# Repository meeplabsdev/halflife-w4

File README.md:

# Music Player
|||
|---|---|

This is a embedded music player, which is designed to be on a desk and display the current track + lyrics over spotify or bluetooth (or others platforms).

# What it is
This project was created for week 4 of [halflife](https://halflife.hackclub.com/)! I designed the schematic and PCB using [KiCad](https://www.kicad.org/), as a hat for the [Orange Pi Zero 3](http://www.orangepi.org/orangepiwiki/index.php/Orange_Pi_Zero_3), which runs embedded linux so I was able to write the firmware in a form much closer to a traditional desktop application (and it can even be tested off the device with the gpio changes printed to the terminal). Originally, I was planning to incorporate the display driver onto the PCB, but I ended up just using a driver board from adafruit since it worked out to be cheaper.

# Hardware
Schematic:

PCB:

|||
|---|---|

# Software
[`firmware/`](firmware/) contains a rust project which can control the board (using wiringpi to set gpio states) and a GUI for the screen. Currently, it is just demo firmware to show how the device could be controlled but when I build this, I could update the firmware to something more useful.

# Case
I also designed a case for this to hold the screen at a reasonable angle, and to keep the boards in the back neat. (red is the screen)

|||
|---|---|

# Cost
This is a rough outline of the cost, see [`BOM.csv`](bom.csv) for more details.

| Part | Cost |
| --- | --- |
| [Screen](https://www.aliexpress.com/i/32772985029.html) | $16.92 |
| [Controller board](https://www.aliexpress.com/i/1005007586011837.html) | $33.00 |
| [Screen controller](https://thepihut.com/products/adafruit-tfp401-hdmi-dvi-decoder-to-40-pin-ttl-breakout-with-touch) | $38.38 |
| [HDMI adapter](https://www.aliexpress.com/item/1005006253497000.html) | $3.19 |
| [Power adapter](https://www.aliexpress.com/item/1005012406854301.html) | $4.05 |
| **Total + Shipping** | **$99.74** |

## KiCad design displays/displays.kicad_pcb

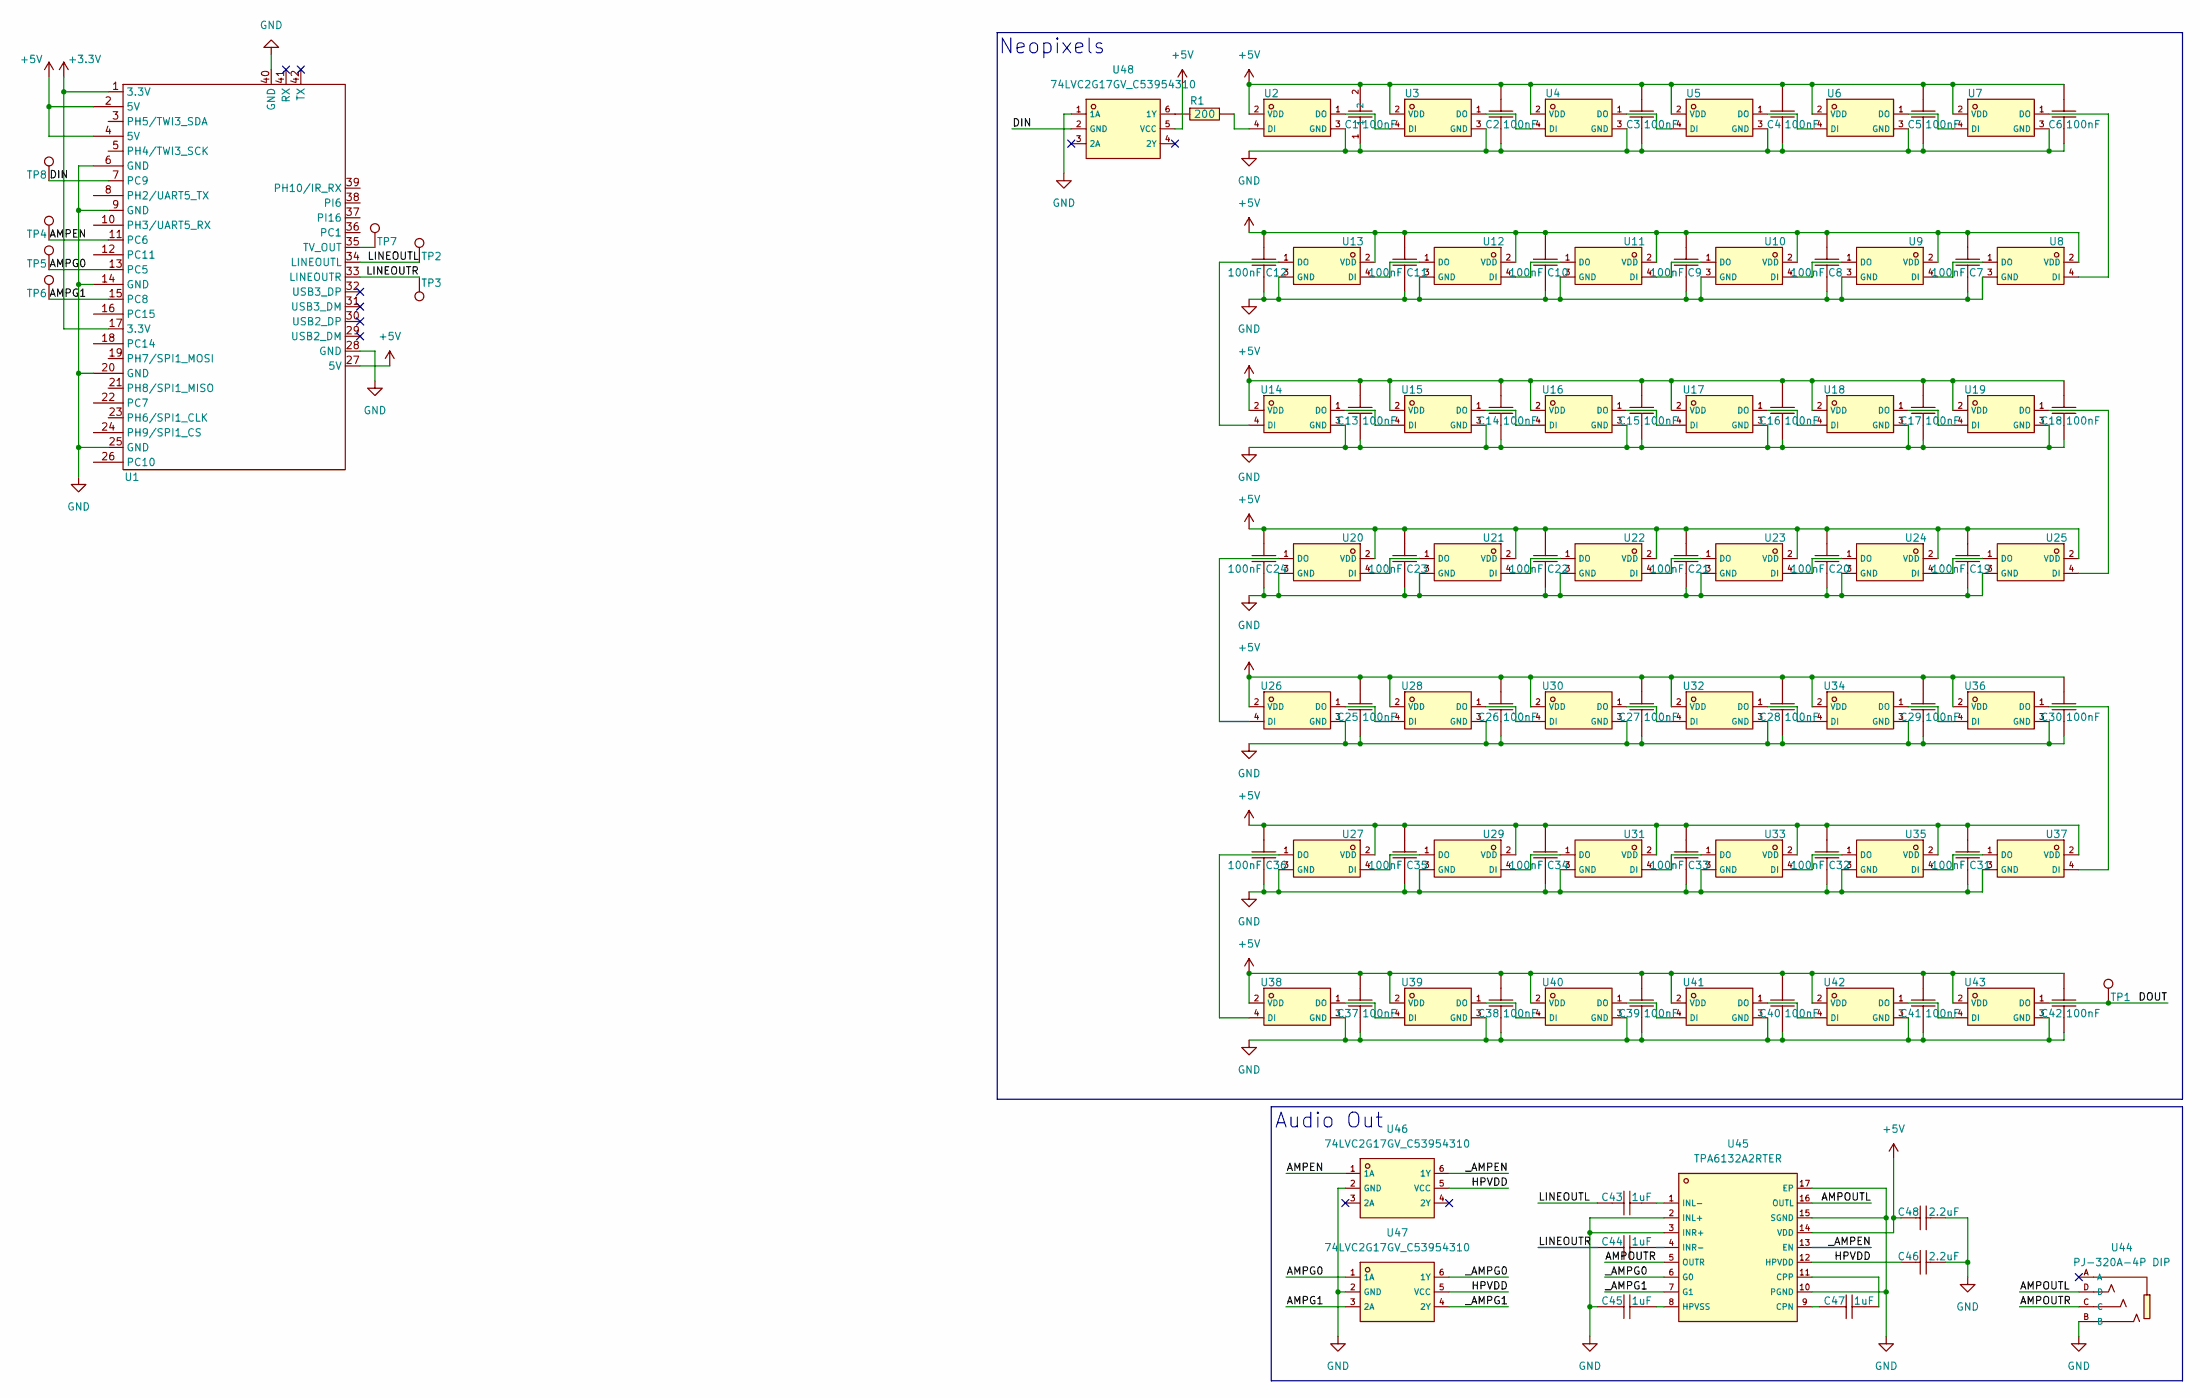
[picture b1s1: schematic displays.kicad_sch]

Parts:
C1, C2, C3, C4, C5, C6, C7, C8, C9, C10, C11, C12, C13, C14, C15, C16, C17, C18, C19, C20, C21, C22, C23, C24, C25, C26, C27, C28, C29, C30, C31, C32, C33, C34, C35, C36, C37, C38, C39, C40, C41, C42: 100nF; C1525_C0402; LCSC C1525
C43, C44, C45, C47: 1uF; C52923_C0402; LCSC C52923
C46, C48: 2.2uF; C23630_C0603; LCSC C23630
R1: 200; C25087_R0402; LCSC C25087
TP1, TP2, TP3, TP4, TP5, TP6, TP7, TP8: TestPoint; SolderWirePad_1x01_SMD_1x2mm
U1: Orange_Pi_Zero_3
U2, U3, U4, U5, U6, U7, U8, U9, U10, U11, U12, U13, U14, U15, U16, U17, U18, U19, U20, U21, U22, U23, U24, U25, U26, U27, U28, U29, U30, U31, U32, U33, U34, U35, U36, U37, U38, U39, U40, U41, U42, U43: TZ-H1010-RGB/A-BU08UF-TA1305NA/W109; C41347988_LED-SMD_4P-L1_0-W1_0_TZ-H1010-RGB-A-BU08UF-TA1305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; LCSC C41347988
U44: PJ-320A-4P DIP; C18185602_AUDIO-TH_PJ-320A-4P-DIP; LCSC C18185602
U45: TPA6132A2RTER; C69901_WQFN-16_L3_0-W3_0-P0_50-TL-EP1_6; LCSC C69901
U46, U47, U48: 74LVC2G17GV_C53954310; C53954310_SOT-23-6_L2_9-W1_6-P0_95-LS2_8-BR-3; LCSC C53954310

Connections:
+3.3V: U1.1 (3.3V), U1.17 (3.3V)
+5V: C1.2, C2.2, C3.2, C4.2, C5.2, C6.2, C7.2, C8.2, C9.2, C10.2, C11.2, C12.2, C13.2, C14.2, C15.2, C16.2, C17.2, C18.2, C19.2, C20.2, C21.2, C22.2, C23.2, C24.2, C25.2, C26.2, C27.2, C28.2, C29.2, C30.2, C31.2, C32.2, C33.2, C34.2, C35.2, C36.2, C37.2, C38.2, C39.2, C40.2, C41.2, C42.2, C48.1, U1.2 (5V), U1.4 (5V), U1.27 (5V), U2.2 (VDD), U3.2 (VDD), U4.2 (VDD), U5.2 (VDD), U6.2 (VDD), U7.2 (VDD), U8.2 (VDD), U9.2 (VDD), U10.2 (VDD), U11.2 (VDD), U12.2 (VDD), U13.2 (VDD), U14.2 (VDD), U15.2 (VDD), U16.2 (VDD), U17.2 (VDD), U18.2 (VDD), U19.2 (VDD), U20.2 (VDD), U21.2 (VDD), U22.2 (VDD), U23.2 (VDD), U24.2 (VDD), U25.2 (VDD), U26.2 (VDD), U27.2 (VDD), U28.2 (VDD), U29.2 (VDD), U30.2 (VDD), U31.2 (VDD), U32.2 (VDD), U33.2 (VDD), U34.2 (VDD), U35.2 (VDD), U36.2 (VDD), U37.2 (VDD), U38.2 (VDD), U39.2 (VDD), U40.2 (VDD), U41.2 (VDD), U42.2 (VDD), U43.2 (VDD), U45.14 (VDD), U48.5 (VCC)
/AMPEN: TP4.1 (1_1), U1.11 (PC6), U46.1 (1A)
/AMPG0: TP5.1 (1_1), U1.13 (PC5), U47.1 (1A)
/AMPG1: TP6.1 (1_1), U1.15 (PC8), U47.3 (2A)
/AMPOUTL: U44.D, U45.16 (OUTL)
/AMPOUTR: U44.C, U45.5 (OUTR)
/DIN: TP8.1 (1_1), U1.7 (PC9), U48.2 (GND)
/DOUT: TP1.1 (1_1), U43.1 (DO)
/HPVDD: C46.1, U45.12 (HPVDD), U46.5 (VCC), U47.5 (VCC)
/LINEOUTL: C43.1, TP2.1 (1_1), U1.34 (LINEOUTL)
/LINEOUTR: C44.1, TP3.1 (1_1), U1.33 (LINEOUTR)
/_AMPEN: U45.13 (EN), U46.6 (1Y)
/_AMPG0: U45.6 (G0), U47.6 (1Y)
/_AMPG1: U45.7 (G1), U47.4 (2Y)
GND: C1.1, C2.1, C3.1, C4.1, C5.1, C6.1, C7.1, C8.1, C9.1, C10.1, C11.1, C12.1, C13.1, C14.1, C15.1, C16.1, C17.1, C18.1, C19.1, C20.1, C21.1, C22.1, C23.1, C24.1, C25.1, C26.1, C27.1, C28.1, C29.1, C30.1, C31.1, C32.1, C33.1, C34.1, C35.1, C36.1, C37.1, C38.1, C39.1, C40.1, C41.1, C42.1, C45.1, C46.2, C48.2, U1.6 (GND), U1.9 (GND), U1.14 (GND), U1.20 (GND), U1.25 (GND), U1.28 (GND), U1.40 (GND), U2.3 (GND), U3.3 (GND), U4.3 (GND), U5.3 (GND), U6.3 (GND), U7.3 (GND), U8.3 (GND), U9.3 (GND), U10.3 (GND), U11.3 (GND), U12.3 (GND), U13.3 (GND), U14.3 (GND), U15.3 (GND), U16.3 (GND), U17.3 (GND), U18.3 (GND), U19.3 (GND), U20.3 (GND), U21.3 (GND), U22.3 (GND), U23.3 (GND), U24.3 (GND), U25.3 (GND), U26.3 (GND), U27.3 (GND), U28.3 (GND), U29.3 (GND), U30.3 (GND), U31.3 (GND), U32.3 (GND), U33.3 (GND), U34.3 (GND), U35.3 (GND), U36.3 (GND), U37.3 (GND), U38.3 (GND), U39.3 (GND), U40.3 (GND), U41.3 (GND), U42.3 (GND), U43.3 (GND), U44.B, U45.2 (INL+), U45.3 (INR+), U45.10 (PGND), U45.15 (SGND), U45.17 (EP), U46.2 (GND), U47.2 (GND), U48.1 (1A)
unnamed: TP7.1 (1_1), U1.35 (TV_OUT)
unnamed: R1.2, U2.4 (DI)
unnamed: U2.1 (DO), U3.4 (DI)
unnamed: U3.1 (DO), U4.4 (DI)
unnamed: U4.1 (DO), U5.4 (DI)
unnamed: U5.1 (DO), U6.4 (DI)
unnamed: U6.1 (DO), U7.4 (DI)
unnamed: U7.1 (DO), U8.4 (DI)
unnamed: U8.1 (DO), U9.4 (DI)
unnamed: U9.1 (DO), U10.4 (DI)
unnamed: U10.1 (DO), U11.4 (DI)
unnamed: U11.1 (DO), U12.4 (DI)
unnamed: U12.1 (DO), U13.4 (DI)
unnamed: U13.1 (DO), U14.4 (DI)
unnamed: U14.1 (DO), U15.4 (DI)
unnamed: U15.1 (DO), U16.4 (DI)
unnamed: U16.1 (DO), U17.4 (DI)
unnamed: U17.1 (DO), U18.4 (DI)
unnamed: U18.1 (DO), U19.4 (DI)
unnamed: U19.1 (DO), U25.4 (DI)
unnamed: U20.4 (DI), U21.1 (DO)
unnamed: U20.1 (DO), U26.4 (DI)
unnamed: U21.4 (DI), U22.1 (DO)
unnamed: U22.4 (DI), U23.1 (DO)
unnamed: U23.4 (DI), U24.1 (DO)
unnamed: U24.4 (DI), U25.1 (DO)
unnamed: U26.1 (DO), U28.4 (DI)
unnamed: U27.4 (DI), U29.1 (DO)
unnamed: U27.1 (DO), U38.4 (DI)
unnamed: U28.1 (DO), U30.4 (DI)
unnamed: U29.4 (DI), U31.1 (DO)
unnamed: U30.1 (DO), U32.4 (DI)
unnamed: U31.4 (DI), U33.1 (DO)
unnamed: U32.1 (DO), U34.4 (DI)
unnamed: U33.4 (DI), U35.1 (DO)
unnamed: U34.1 (DO), U36.4 (DI)
unnamed: U35.4 (DI), U37.1 (DO)
unnamed: U36.1 (DO), U37.4 (DI)
unnamed: U38.1 (DO), U39.4 (DI)
unnamed: U39.1 (DO), U40.4 (DI)
unnamed: U40.1 (DO), U41.4 (DI)
unnamed: U41.1 (DO), U42.4 (DI)
unnamed: U42.1 (DO), U43.4 (DI)
unnamed: C47.1, U45.9 (CPN)
unnamed: C47.2, U45.11 (CPP)
unnamed: C45.2, U45.8 (HPVSS)
unnamed: C43.2, U45.1 (INL-)
unnamed: C44.2, U45.4 (INR-)
unnamed: R1.1, U48.6 (1Y)

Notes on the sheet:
Audio Out
Neopixels

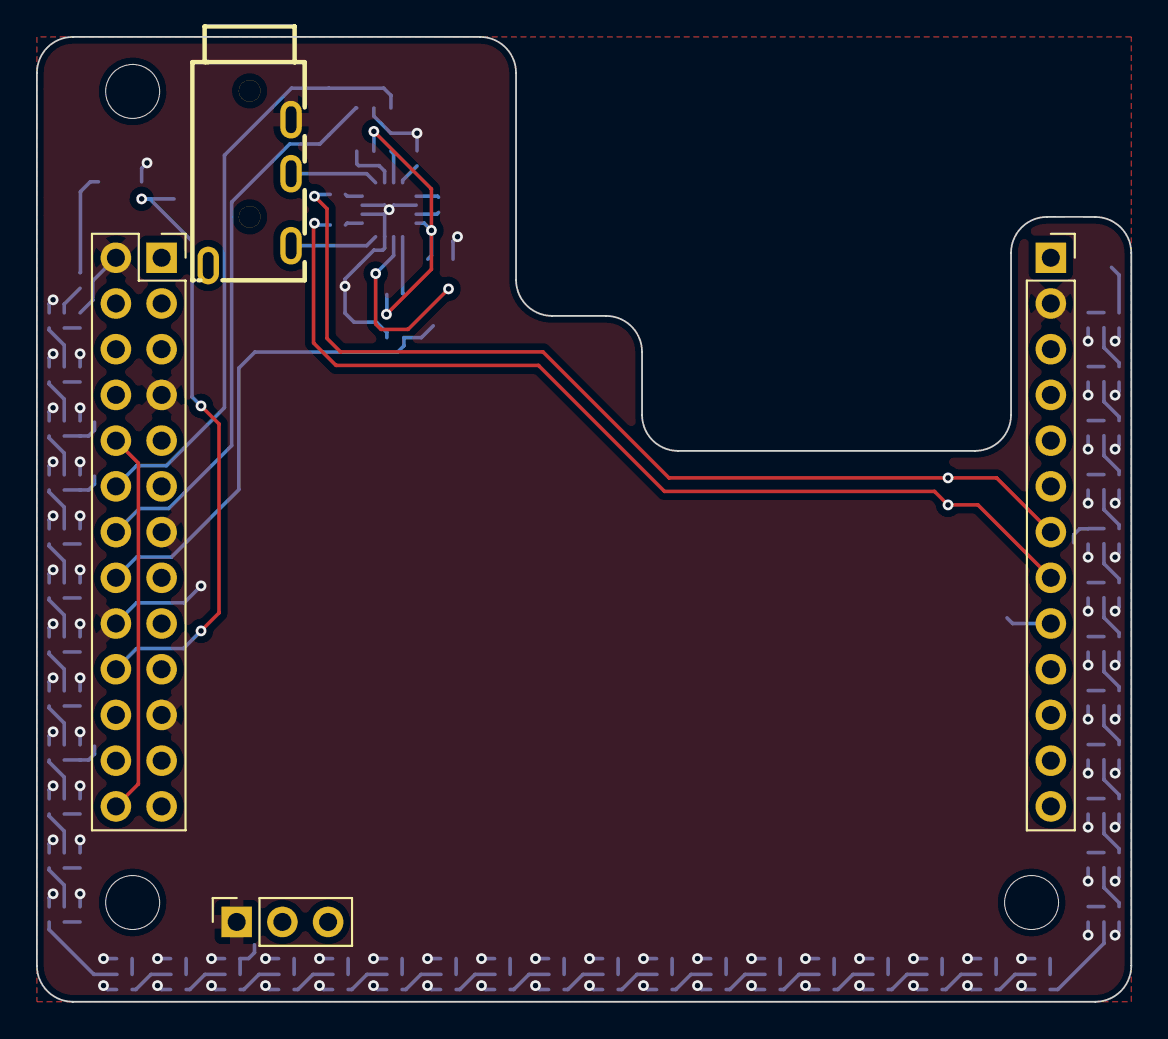
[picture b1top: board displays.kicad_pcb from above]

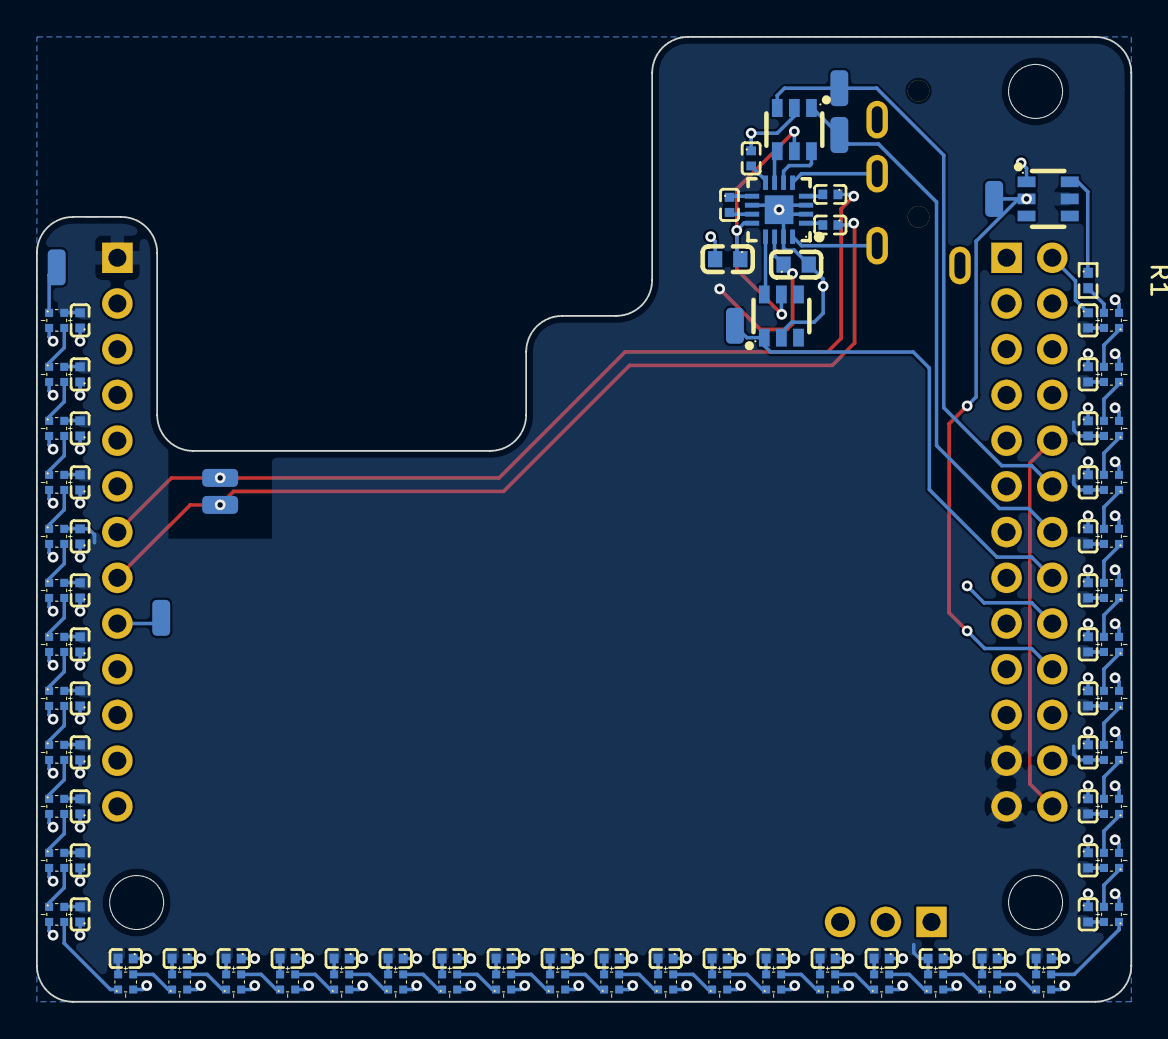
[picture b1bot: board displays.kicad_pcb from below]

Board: 2 copper layers, 60.8 x 53.6 mm, 105 parts (103 on the bottom side), 65 nets.

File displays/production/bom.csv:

Designator,Footprint,Quantity,Value,LCSC Part #
"C1, C10, C11, C12, C13, C14, C15, C16, C17, C18, C19, C2, C20, C21, C22, C23, C24, C25, C26, C27, C28, C29, C3, C30, C31, C32, C33, C34, C35, C36, C37, C38, C39, C4, C40, C41, C42, C5, C6, C7, C8, C9",C1525_C0402,42,100nF,C1525
"C43, C44, C45, C47",C52923_C0402,4,1uF,C52923
"C46, C48",C23630_C0603,2,2.2uF,C23630
R1,C25087_R0402,1,200,C25087
"TP1, TP2, TP3, TP4, TP5, TP6, TP7, TP8",SolderWirePad_1x01_SMD_1x2mm,8,TestPoint,
U1,Orange_Pi_Zero_3,1,~,
"U10, U11, U12, U13, U14, U15, U16, U17, U18, U19, U2, U20, U21, U22, U23, U24, U25, U26, U27, U28, U29, U3, U30, U31, U32, U33, U34, U35, U36, U37, U38, U39, U4, U40, U41, U42, U43, U5, U6, U7, U8, U9",C41347988_LED-SMD_4P-L1_0-W1_0_TZ-H1010-RGB-A-BU08UF-TA1305NA-W109,42,TZ-H1010-RGB/A-BU08UF-TA1305NA/W109,C41347988
U44,C18185602_AUDIO-TH_PJ-320A-4P-DIP,1,PJ-320A-4P DIP,C18185602
U45,C69901_WQFN-16_L3_0-W3_0-P0_50-TL-EP1_6,1,TPA6132A2RTER,C69901
"U46, U47, U48",C53954310_SOT-23-6_L2_9-W1_6-P0_95-LS2_8-BR-3,3,74LVC2G17GV_C53954310,C53954310
